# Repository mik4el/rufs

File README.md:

# rufs
Collection of hacks and iterative builds for RUFS-1, the satellite to bring Rufs the Space Lion in to space (http://rufsklubben.se/).

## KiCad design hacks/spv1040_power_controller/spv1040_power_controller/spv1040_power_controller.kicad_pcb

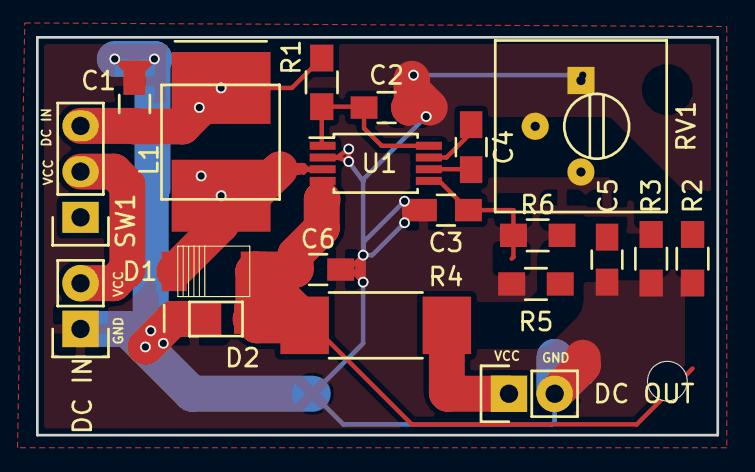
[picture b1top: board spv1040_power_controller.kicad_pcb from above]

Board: 2 copper layers, 37.8 x 22.1 mm, 20 parts (0 on the bottom side), 10 nets.

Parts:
C1, C2, C5, C6: 10uF; C_0805_HandSoldering
C3: 1nF; C_0805_HandSoldering
C4: 1uF; C_0805_HandSoldering
D1: D_Schottky; SOD-128
D2: TVS; STmite_flat_DO216-AA
DC IN: DC IN; Pin_Header_Straight_1x02
DC OUT: DC OUT; Pin_Header_Straight_1x02
L1: 10uH; XAL6060
R1, R2, R3: 1K; R_0805_HandSoldering
R4: 10m; R_2512_HandSoldering
R5: 1M; R_0805_HandSoldering
R6: 330K; R_0805_HandSoldering
RV1: POT; Potentiometer_Trimmer-Suntan-TSR-3386P
SW1: SWITCH_INV; Pin_Header_Straight_1x03
U1: SPV1040; TSSOP-8_4.4x3mm_Pitch0.65mm

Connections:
GND: C1.2, C2.2, C3.2, C5.2, C6.2, D2.2, DC IN.1, DC OUT.2, R6.2, RV1.2, RV1.3, U1.2
unnamed: C1.1, L1.2, R1.1, RV1.1, SW1.3
unnamed: C2.1, R1.2, U1.1, U1.8
unnamed: C3.1, R5.2, R6.1, U1.5
unnamed: C4.1, R2.2, U1.7
unnamed: C4.2, R3.2, U1.6
unnamed: C5.1, DC OUT.1, R3.1, R4.1, R5.1
unnamed: C6.1, D1.1, D2.1, R2.1, R4.2, U1.4
unnamed: D1.2, L1.1, U1.3
VCC: DC IN.2, SW1.2

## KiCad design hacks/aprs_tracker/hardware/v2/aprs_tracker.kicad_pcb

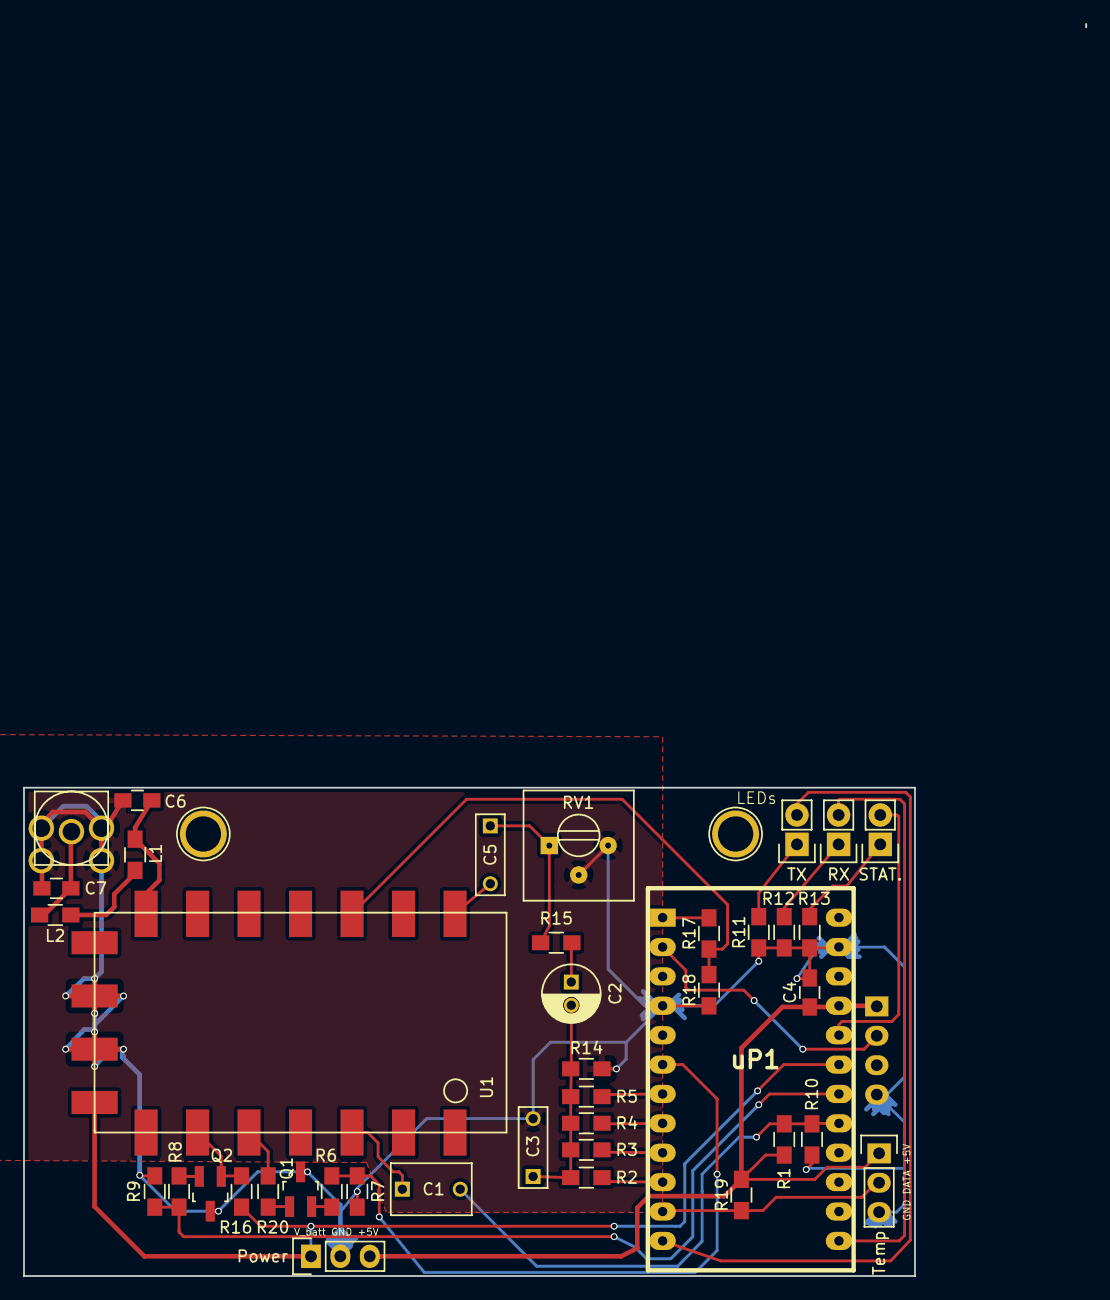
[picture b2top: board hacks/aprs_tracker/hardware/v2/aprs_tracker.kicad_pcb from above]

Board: 2 copper layers, 91.8 x 108.2 mm, 41 parts (1 on the bottom side), 33 nets.

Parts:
C1: 1uF; C_Rect_L7_W4.5_P5
C2: 4.7uF; C_Radial_D5_L11_P2
C3, C5: 100nF; C_Rect_L7_W2.5_P5
C4: 100nF; C_0805_HandSoldering
C6, C7: 15pF; C_0805_HandSoldering
J1: SMA; sma_female_top
L1, L2: 0.027uH; R_0805_HandSoldering
P3: GPS; ublox_gps_breakout
Power: POWER; Pin_Header_Straight_1x03
Q1, Q2: 2N7002; SOT-23_Handsoldering
R1, R10, R15: 100K; R_0805_HandSoldering
R2: 1K 1%; R_0805_HandSoldering
R3: 2K2 1%; R_0805_HandSoldering
R4: 3K9 1%; R_0805_HandSoldering
R5: 8K2 1%; R_0805_HandSoldering
R6, R7, R8, R9: 1K; R_0805_HandSoldering
R11, R12, R13: 3K3; R_0805_HandSoldering
R14: 270 1%; R_0805_HandSoldering
R16, R17, R20: 10K; R_0805_HandSoldering
R18: 20K; R_0805_HandSoldering
R19: 4.7K; R_0805_HandSoldering
RV1: 10K; Potentiometer_Trimmer-Suntan-TSR-3386P
RX: RX (RED); Pin_Header_Straight_1x02
STAT.: STATUS (GREEN); Pin_Header_Straight_1x02
TX: TX (GREEN); Pin_Header_Straight_1x02
Temp: TEMPERATURE; Pin_Header_Straight_1x03
U1: DRA818V; dra818v
uP1: Pro Mini 5V 16MHz; ARDUINO_PRO_MINI

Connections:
+5V: C4.1, P3.1, Power.3, R1.2, R19.1, Temp.1, uP1.21
/AUDIO_IN: C1.2, R1.1, R10.1, uP1.17
/D4: R5.2, uP1.7
/D5: R4.2, uP1.8
/D6: R3.2, uP1.9
/D7: R2.2, uP1.10
/D9: TX.2, uP1.12
/D10: RX.2, uP1.13
/GPS_RX: P3.2, uP1.2
/LINE_LEVEL_IN: C1.1, U1.3
/MIC_LEVEL_OUT: C5.1, R15.1, RV1.1
/PTT_CONTROL: R6.2, R7.2, uP1.6
/PTT_V+: Q1.1, R20.2
/RADIO_PD: Q2.1, R16.2, U1.6
/RADIO_PD_CONTROL: R8.2, R9.2, uP1.18
/RADIO_TX: R17.1, R18.1, U1.16
/STATUS_LED: STAT..2, uP1.20
/TEMP_DATA: R19.2, Temp.2, uP1.11
/V_BATT: Power.1, R16.1, U1.8, uP1.19
GND: C3.2, C4.2, C6.2, C7.2, J1.2, J1.3, J1.4, J1.5, P3.4, Power.2, Q1.3, Q2.3, R7.1, R9.1, R10.2, R11.1, R12.1, R13.1, R14.2, R18.2, RV1.2, RV1.3, Temp.3, U1.9, U1.10, uP1.4, uP1.23
unnamed: C2.1, R15.2
unnamed: C2.2, C3.1, R2.1, R3.1, R4.1, R5.1, R14.1
unnamed: C5.2, U1.18
unnamed: C6.1, L1.1, U1.12
unnamed: C7.1, J1.1, L2.2
unnamed: R11.2, TX.1
unnamed: R12.2, RX.1
unnamed: R13.2, STAT..1
unnamed: L1.2, L2.1
unnamed: Q1.2, R6.1
unnamed: Q2.2, R8.1
unnamed: R17.2, uP1.1
unnamed: R20.1, U1.5

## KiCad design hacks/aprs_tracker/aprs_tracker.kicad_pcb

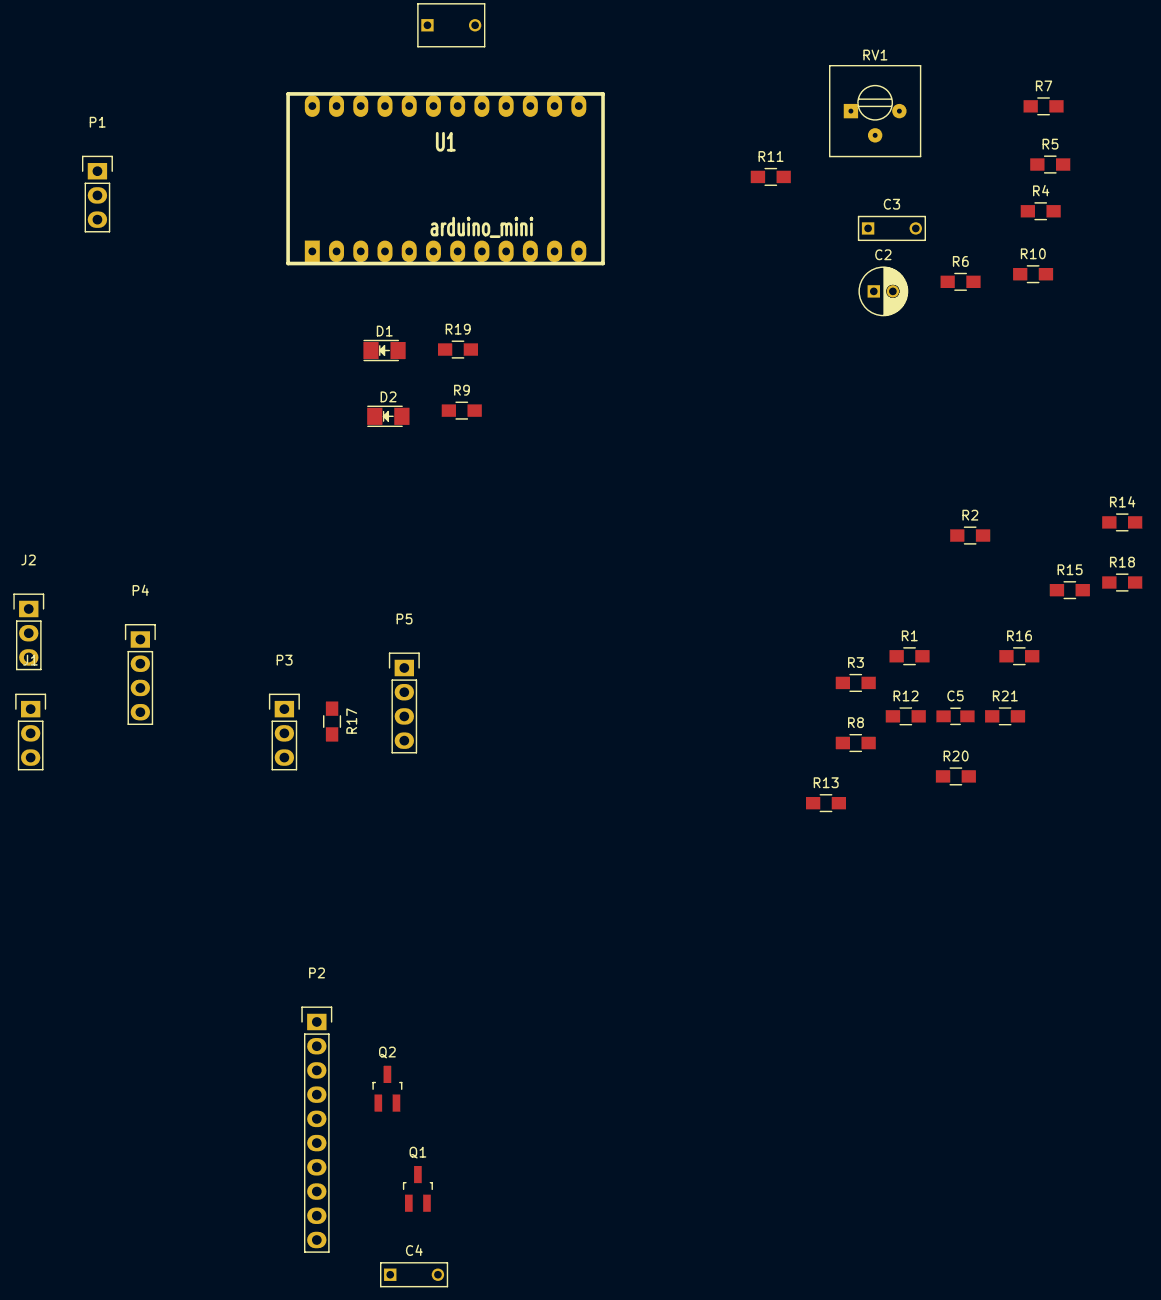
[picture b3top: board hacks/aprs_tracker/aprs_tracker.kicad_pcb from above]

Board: 2 copper layers, 39 parts (0 on the bottom side), 26 nets, no tracks yet.

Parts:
C1: 1uF; C_Rect_L7_W4.5_P5
C2: 4.7uF; C_Radial_D5_L11_P2
C3, C4: 100nF; C_Rect_L7_W2.5_P5
C5: 100nF; C_0805_HandSoldering
D1: TX (GREEN); LED_1206
D2: RX (RED); LED_1206
J1: 3.5mm Stereo Jack; Pin_Header_Straight_1x03
J2: 2.5mm Stereo Jack; Pin_Header_Straight_1x03
P1: POWER; Pin_Header_Straight_1x03
P2: RADIO; Pin_Header_Straight_1x10
P3: TEMPERATURE; Pin_Header_Straight_1x03
P4: BAOFENG; Pin_Header_Straight_1x04
P5: GPS; Pin_Header_Straight_1x04
Q1, Q2: 2N7002; SOT-23_Handsoldering
R1, R2, R12, R18: 1K; R_0805_HandSoldering
R3, R8, R11: 100K; R_0805_HandSoldering
R4: 1K 1%; R_0805_HandSoldering
R5: 2K2 1%; R_0805_HandSoldering
R6: 3K9 1%; R_0805_HandSoldering
R7: 8K2 1%; R_0805_HandSoldering
R9, R19: 3K3; R_0805_HandSoldering
R10: 270 1%; R_0805_HandSoldering
R13, R14, R20, R21: 10K; R_0805_HandSoldering
R15, R16: 20K; R_0805_HandSoldering
R17: 4.7K; R_0805_HandSoldering
RV1: 10K; Potentiometer_Trimmer-Suntan-TSR-3386P
U1: arduino_mini; ARDUINO_PRO_MINI

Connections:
+5V: C5.1, P1.3, P3.1, P5.1, R3.2, R17.1, U1.12
/AUDIO_IN: C1.2, R3.1, R8.1, U1.4
/D4: R7.2, U1.22
/D5: R6.2, U1.23
/D6: R5.2, U1.24
/GPS_RX: P5.3, U1.17
/LINE_LEVEL_IN: C1.1, P2.2
/MIC_LEVEL_OUT: C4.2, R11.1, RV1.1
/PTT_CONTROL: R1.2, R2.2, U1.21
/PTT_V+: Q1.1, R20.2
/RADIO_PD: P2.4, Q2.1, R21.2
/RADIO_PD_CONTROL: R12.2, R18.2, U1.5
/RADIO_TX: P2.8, R14.1, R16.1
/TEMP_DATA: P3.2, R17.2
/V_BATT: P1.1, P2.6, R21.1, U1.6
GND: C3.2, C5.2, P1.2, P2.7, P3.3, P5.4, Q1.3, Q2.3, R2.1, R8.2, R9.1, R10.2, R15.1, R16.2, R18.1, R19.1, RV1.2, RV1.3, U1.14, U1.19
unnamed: C2.1, R11.2
unnamed: C2.2, C3.1, R4.1, R5.1, R6.1, R7.1, R10.1
unnamed: C4.1, P2.10
unnamed: D1.1, R19.2
unnamed: D2.1, R9.2
unnamed: P2.3, R20.1
unnamed: P5.2, R13.1, R15.2
unnamed: Q1.2, R1.1
unnamed: Q2.2, R12.1
unnamed: R14.2, U1.16

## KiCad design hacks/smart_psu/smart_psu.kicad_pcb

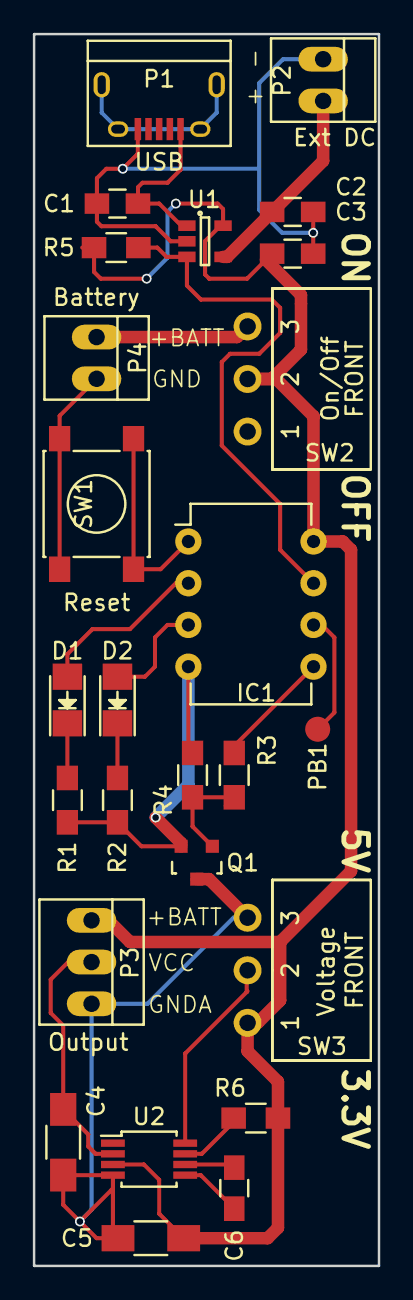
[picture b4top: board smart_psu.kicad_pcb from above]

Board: 2 copper layers, 21.0 x 75.0 mm, 25 parts (0 on the bottom side), 19 nets.

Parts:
C1, C2, C3, C6: C_0805_HandSoldering
C4, C5: C_1206_HandSoldering
D1, D2: LED_1206
IC1: DIP-8_W7.62mm
P1: USB; USB_Micro-B
P2: Ext DC; PINHEAD1-2
P3: Output; PINHEAD1-3
P4: Battery; PINHEAD1-2
Q1: SOT-23
R1, R2, R3, R4, R5, R6: R_0805_HandSoldering
SW1: Reset; SW_SPST_PTS645
SW2: On/Off; spdt_slide_switch_angled
SW3: Voltage; spdt_slide_switch_angled
U1: SOT-23-5
U2: MSOP-8_3x3mm_Pitch0.65mm

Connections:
+BATT: C3.1, C5.1, IC1.8, P3.1, R5.2, R6.2, SW2.2, SW3.1, U1.5, U2.3
GND: C1.1, C2.2, C3.2, IC1.4, P1.5, P2.1, P4.2, Q1.3, R1.2, R2.2, R4.2, SW1.1, U1.2
GNDA: C4.2, C5.2, P3.3, Q1.1, SW3.3, U2.4
unnamed: C1.2, P1.1, U1.1
unnamed: C2.1, P2.2, U1.4
unnamed: C6.1, U2.6
unnamed: C6.2, U2.5
unnamed: D1.1, R1.1
unnamed: D1.2, IC1.2
unnamed: D2.1, R2.1
unnamed: D2.2, IC1.3
unnamed: IC1.1, SW1.2
unnamed: IC1.5, R3.2
unnamed: IC1.7, R5.1, U1.3
unnamed: P4.1, SW2.3
unnamed: Q1.2, R3.1, R4.1
unnamed: R6.1, U2.7
unnamed: SW3.2, U2.8
VCC: C4.1, P3.2, U2.2

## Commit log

2015-12-06 RF blink hack added.
2015-12-06 Verified that it works.
2015-12-06 Added rf_temp_link after first test
2015-12-06 Updated gitignore
2015-12-08 Message making using strings
2015-12-08 Better string handling on receiver
2015-12-08 created and tested rf_temp_sensor
2015-12-09 tested and cleaned up message
2015-12-10 added voltage metering
2015-12-11 aAdded second termometer
2015-12-11 Added sleep mode
2015-12-12 Picture of circuit
2015-12-13 added python logger
2015-12-19 fixes for sensor live test
2015-12-19 pictures and video of logger
2015-12-19 tuned python script for raspi use
2015-12-21 updated pictures for tested equipment
2016-01-03 First iteration of kicad schema and pcb
2016-01-03 moved directories for pcb and schema files
2016-01-03 added picture of pcb
2016-01-05 started files
2016-01-05 simple psu for 5v and 3.3v first schema
2016-01-05 simplified psu to start with 5v first
2016-01-09 tested schema and made prototype incl pics and video
2016-01-09 fixed file ending
2016-01-09 battery test notes
2016-01-11 finished and tested charging with build
2016-01-11 mounted psu in rf_temp
2016-01-11 added osx adress in save_serial script
2016-01-12 tested soldering smds
2016-01-12 smd solder board layout
2016-01-12 breadboarded and programmed attiny85 blink including videos
2016-01-12 one more adress to save serial
2016-01-13 started attiny85 voltage meter
2016-01-13 added timer on off
2016-01-13 refined feedback and tested reset pin to restart
2016-01-13 added mosfet switch and refined
2016-01-14 made schema and pics of hack
2016-01-15 breadboarded max1555 and made kicad component and schema
2016-01-15 made schema for mcp1253 breadboard
2016-01-16 breadboarded and updated schema
2016-01-17 added smart_psu schema
2016-01-17 added schema for smart psu
2016-01-18 tested and updated schema
2016-01-19 started associating footprints
2016-01-19 started with pcb
2016-01-19 started laying out pcb
2016-01-20 pcb layouayout done
2016-01-20 started laying tracks
2016-01-20 first iteration ready
2016-01-21 printed out layout to verify
2016-01-21 fixed exports and ordered pcb v01
2016-01-25 added picture of ready pcb
2016-01-25 added all external components
2016-01-25 ready with schematic and symbol
2016-01-25 made dra818v footprint and layed out board
2016-01-26 finished v01 and ordered pcb
2016-02-01 solar cell experiments
2016-02-01 made schematic for spv1040 to be tested
2016-02-03 first schema for spv1040, tested unsuccesfully
2016-02-03 new solar experiment
2016-02-03 refined schematic and added documentation
2016-02-04 assembled and tested smart psu pcb
2016-02-05 reconfigured sensor to work with smart_psu
2016-02-05 updated timer code and tested on pcb
2016-02-10 refined temp sensor for test
2016-02-10 made aprsdroid cable
2016-02-11 made succesful outside test with aprsdroid
2016-02-16 made it possible to use longer on periods
2016-02-17 tested serial communication between pro minis
2016-02-18 played around with avr compiling
2016-02-19 made succesful microaprs test
2016-02-19 microaprs send and receive working
2016-02-21 playing around with libaprs
2016-02-23 testing libaprs with sensors
2016-02-24 performance verified on breadboard indoors
2016-02-24 updated schema for aprs tracker to match tested version
2016-02-25 updated aprs packets after test
2016-02-25 made minute update position
2016-02-25 added debug flag
2016-02-26 added pictures
2016-02-28 verified function of updated libaprs tracker and started new project aprs_tracker.ino
2016-02-29 testing dra818
2016-03-01 aprs_tracker works with dra818
2016-03-02 sleep mode working and updated circuit
2016-03-03 ready for test with pro mini
2016-03-05 started making pcb
2016-03-07 made v2 hardware separation
2016-03-08 started pcb placing
2016-03-09 initial placement ready
2016-03-11 placed holes for box
2016-03-12 placement with holes ready
2016-03-13 placement and wiring ready and tested
2016-03-13 board iter 1 ready
2016-03-13 ordered pcbs
2016-03-16 spv1040 test done
2016-03-16 started pcb for spv1040
2016-03-17 started assigning components
2016-03-17 made footprints and started pcb
2016-03-18 made placement and wiring
2016-03-18 pcb ready for test
2016-03-22 added trim pot to mpp-set
2016-03-22 ordered spv1040 pcb
2016-03-22 some notes form spv1040 tests
2016-04-11 aprs_tracker working
2016-04-18 tracker and power controller ready with pictures
2016-05-16 improve sending performance
2016-10-12 building 3rd smart psu
2016-10-18 defaults in comments for different gadgets
